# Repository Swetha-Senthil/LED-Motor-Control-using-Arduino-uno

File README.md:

# LED-Motor-Control-using-Arduino-uno

# Arduino Motor and LED Control

This project demonstrates controlling a DC motor and an LED using an Arduino. The motor direction is controlled via serial input, and the LED blinks at a fixed interval without blocking execution.

## Features
- **Non-blocking LED Blink**: Uses `millis()` instead of `delay()`.
- **Motor Direction Control**: Serial commands (`F`, `R`, `S`) control motor movement.
- **PWM Speed Control**: Motor speed can be adjusted via the `motorSpeed` pin.
- **Designed PCB Using KiCad**: Custom PCB layout created in KiCad.
- **Simulated in Tinkercad**: Verified functionality using Tinkercad simulation.

## Components Used
- **Arduino Uno**
- **DC Motor**
- **L293D Motor Driver**
- **LED**
- **Resistor-250 ohms**
- **External Power Supply-9V battery**

## Circuit Connections
| Component   | Pin Connection |
|------------|---------------|
| LED        | 7 (Digital)   |
| Motor IN1  | 8 (Digital)   |
| Motor IN2  | 9 (Digital)   |
| PWM Speed  | 10 (PWM)      |

## Code Overview
The Arduino sketch:
- Initializes pins and sets a default motor speed.
- Toggles the LED every 1 second without using `delay()`.
- Reads serial input for motor control:
  - `F` → Forward
  - `R` → Reverse
  - `S` → Stop

## How to Use
1. **Upload the code** to an Arduino Uno.
2. **Send Serial Commands** (`F`, `R`, `S`) via Serial Monitor.
3. Observe motor direction changes and LED blinking.

## PCB Design
- Designed using **KiCad** for a compact layout.
- Integrated motor driver and control logic.
- Optimized for easy soldering and assembly.

## Simulation
- The circuit was **simulated in Tinkercad** to verify its functionality before hardware implementation.

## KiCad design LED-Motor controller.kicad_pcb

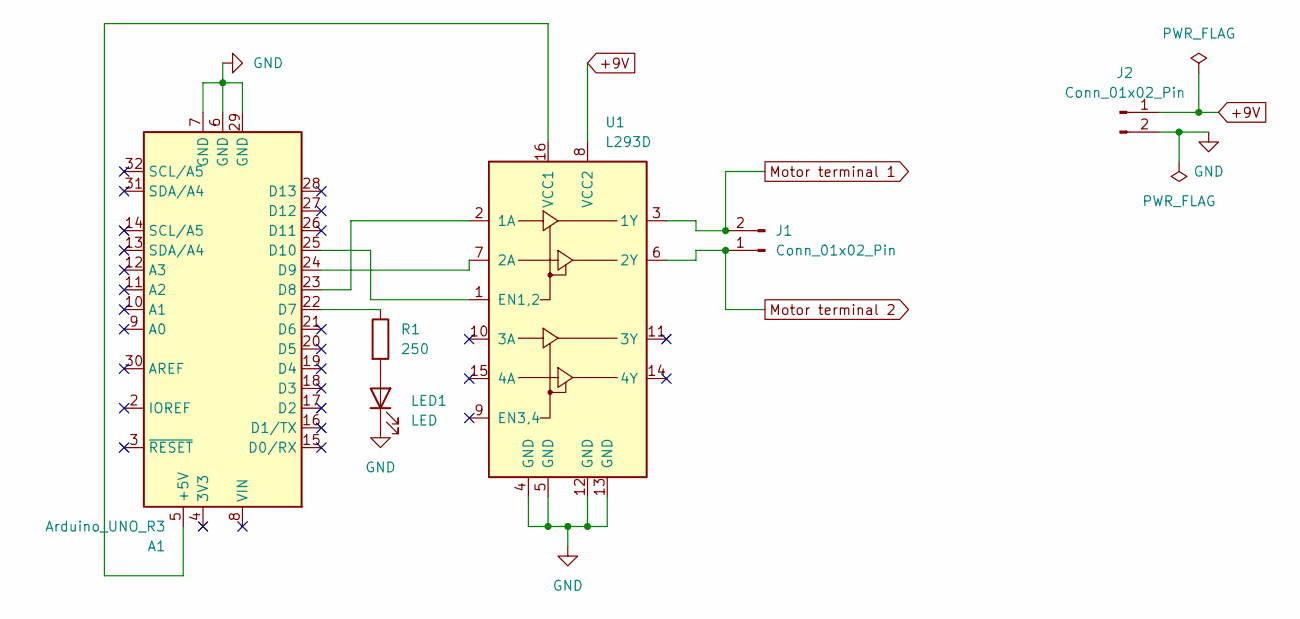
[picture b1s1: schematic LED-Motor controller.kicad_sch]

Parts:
A1: Arduino_UNO_R3
J1, J2: Conn_01x02_Pin; PinHeader_1x02_P2.54mm_Vertical
LED1: LED; LED_D3.0mm
R1: 250; R_Axial_DIN0204_L3.6mm_D1.6mm_P2.54mm_Vertical
U1: L293D; DIP-16_W7.62mm

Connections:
+9V: J2.1, U1.8 (VCC2)
GND: A1.6 (GND), A1.7 (GND), A1.29 (GND), J2.2, LED1.1 (K), U1.4 (GND), U1.5 (GND), U1.12 (GND), U1.13 (GND)
Motor terminal 1: J1.2, U1.3 (1Y)
Motor terminal 2: J1.1, U1.6 (2Y)
unnamed: A1.5 (+5V), U1.16 (VCC1)
unnamed: A1.22 (D7), R1.1
unnamed: A1.23 (D8), U1.2 (1A)
unnamed: A1.24 (D9), U1.7 (2A)
unnamed: A1.25 (D10), U1.1 (EN1,2)
unnamed: LED1.2 (A), R1.2

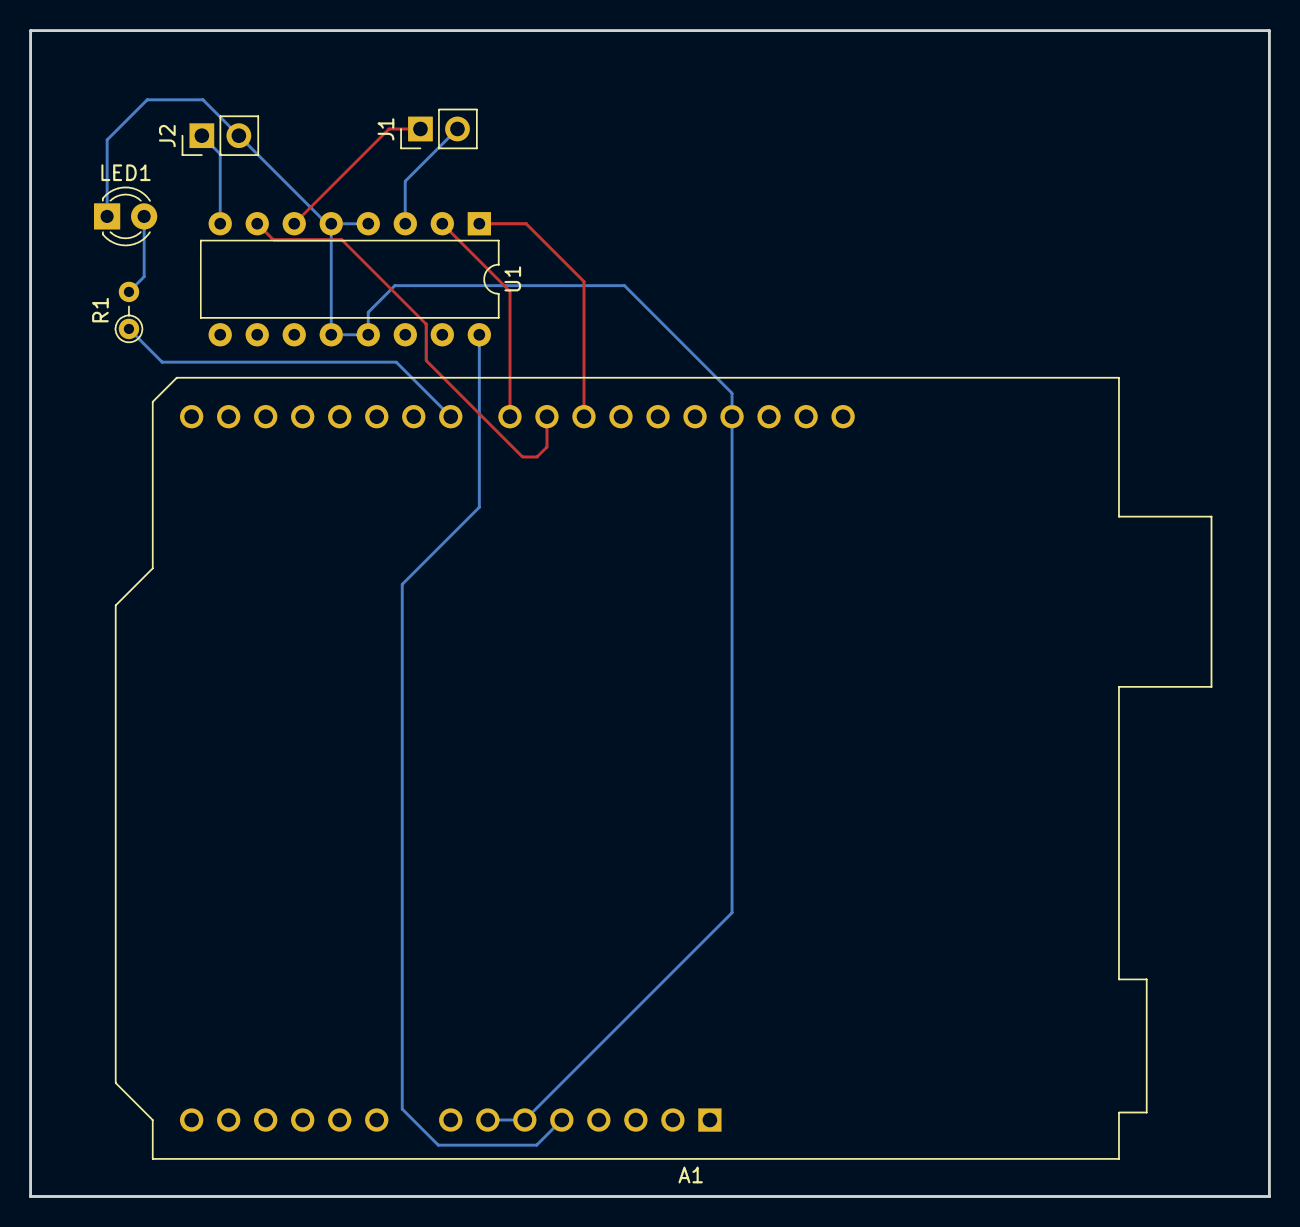
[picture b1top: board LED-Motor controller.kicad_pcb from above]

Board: 2 copper layers, 85.0 x 80.0 mm, 6 parts (0 on the bottom side), 10 nets.

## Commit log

2025-02-06 Create Code.ino
    Added code for simultaneous control of LED and motor using Arduino uno.
